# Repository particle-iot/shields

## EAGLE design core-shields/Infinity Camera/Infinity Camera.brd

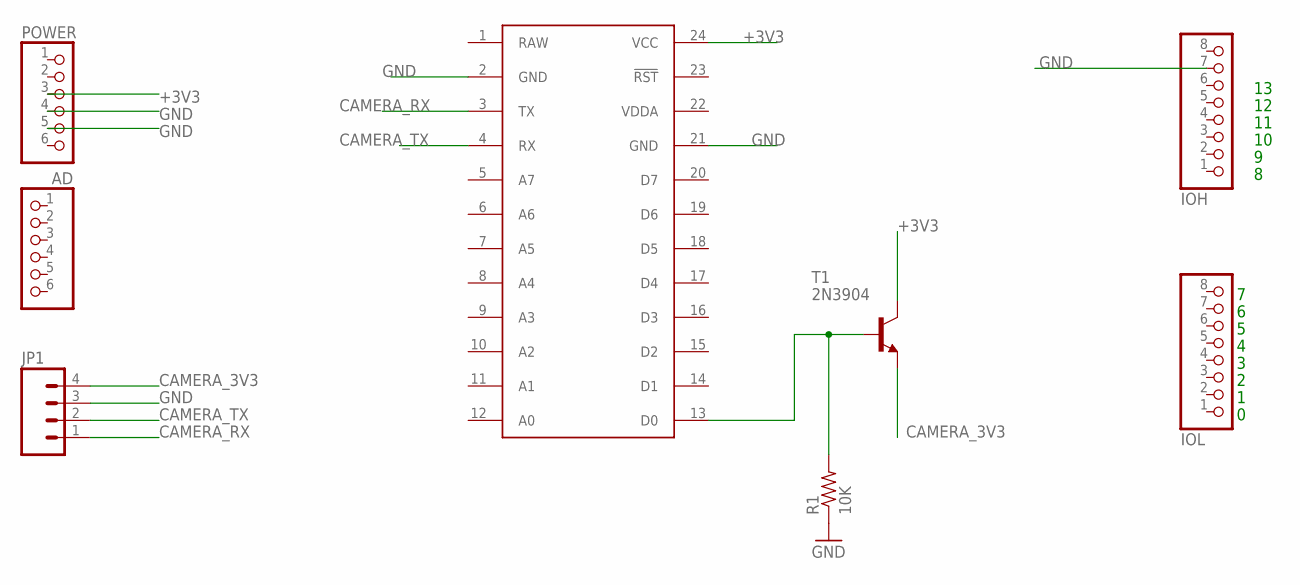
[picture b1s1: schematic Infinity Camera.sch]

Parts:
AD: PINHD-1X6; 1X06
IOH: PINHD-1X8; 1X08
IOL: PINHD-1X8; 1X08
JP1: M04PTH; 1X04
POWER: PINHD-1X6; 1X06
R1: 10K; AXIAL-0.4
T1: 2N3904; TO92
U$1: SPARK_CORECORE; SPARK_CORE

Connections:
+3V3: POWER.3, T1.1 (C), U$1.24 (VCC)
CAMERA_3V3: JP1.4, T1.3 (E)
CAMERA_RX: JP1.1, U$1.3 (TX)
CAMERA_TX: JP1.2, U$1.4 (RX)
GND: IOH.7, JP1.3, POWER.4, POWER.5, R1.P$1 (1), U$1.2 (GND), U$1.21 (GND)
unnamed: R1.P$2 (2), T1.2 (B), U$1.13 (D0)
RAW: U$1.1 (RAW)
VDDA: U$1.22 (VDDA)

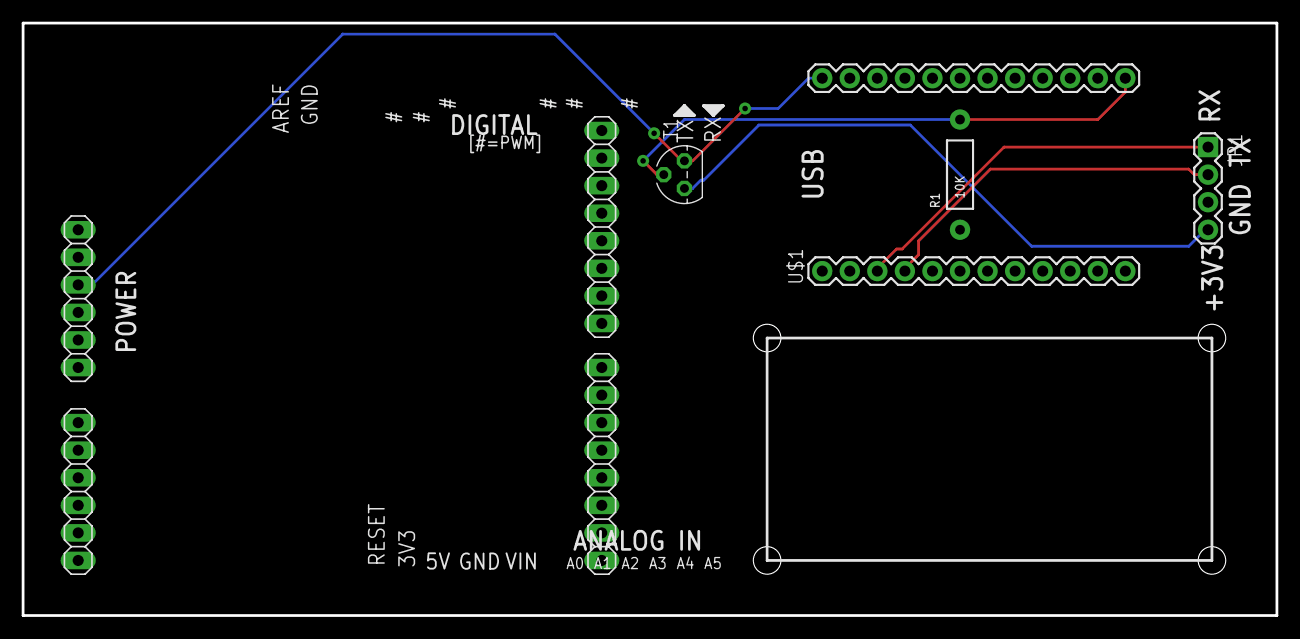
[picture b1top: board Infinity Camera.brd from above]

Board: 2 copper layers, 115.6 x 54.6 mm, 10 parts (0 on the bottom side), 6 nets.

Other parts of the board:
U$2, U$3: SPARK_LOGO

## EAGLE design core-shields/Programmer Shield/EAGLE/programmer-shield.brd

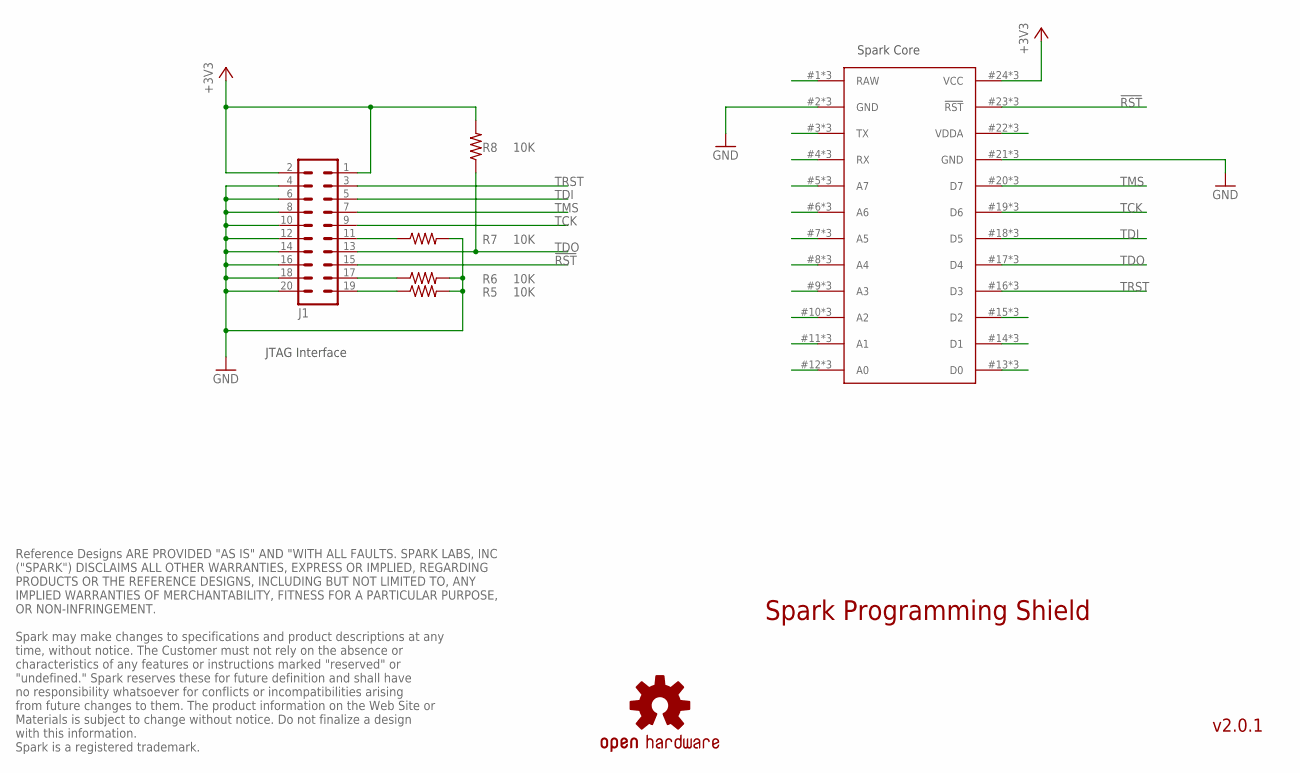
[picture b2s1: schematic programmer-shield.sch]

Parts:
J1: ML20
LOGO1: OSHW-LOGOM; OSHW-LOGO-M
R5, R6, R7, R8: 10K; AXIAL-0.3
U$1: SPARK_CORE; SPARK_CORE_STACKABLE

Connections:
!RST: J1.15, U$1.23 (!RST), U$1.#23 (!RST), U$1.@23 (!RST)
+3V3: J1.1, J1.2, R8.P$2 (2), U$1.24 (VCC), U$1.#24 (VCC), U$1.@24 (VCC)
GND: J1.4, J1.6, J1.8, J1.10, J1.12, J1.14, J1.16, J1.18, J1.20, R5.P$2 (2), R6.P$2 (2), R7.P$2 (2), U$1.2 (GND), U$1.21 (GND), U$1.#2 (GND), U$1.#21 (GND), U$1.@2 (GND), U$1.@21 (GND)
unnamed: U$1.1 (RAW), U$1.#1 (RAW), U$1.@1 (RAW)
unnamed: U$1.3 (TX), U$1.#3 (TX), U$1.@3 (TX)
unnamed: U$1.4 (RX), U$1.#4 (RX), U$1.@4 (RX)
unnamed: U$1.5 (A7), U$1.#5 (A7), U$1.@5 (A7)
unnamed: U$1.6 (A6), U$1.#6 (A6), U$1.@6 (A6)
unnamed: U$1.7 (A5), U$1.#7 (A5), U$1.@7 (A5)
unnamed: U$1.8 (A4), U$1.#8 (A4), U$1.@8 (A4)
unnamed: U$1.9 (A3), U$1.#9 (A3), U$1.@9 (A3)
unnamed: U$1.10 (A2), U$1.#10 (A2), U$1.@10 (A2)
unnamed: U$1.11 (A1), U$1.#11 (A1), U$1.@11 (A1)
unnamed: U$1.12 (A0), U$1.#12 (A0), U$1.@12 (A0)
unnamed: U$1.13 (D0), U$1.#13 (D0), U$1.@13 (D0)
unnamed: J1.19, R5.P$1 (1)
unnamed: J1.17, R6.P$1 (1)
unnamed: J1.11, R7.P$1 (1)
unnamed: U$1.14 (D1), U$1.#14 (D1), U$1.@14 (D1)
unnamed: U$1.15 (D2), U$1.#15 (D2), U$1.@15 (D2)
unnamed: U$1.22 (VDDA), U$1.#22 (VDDA), U$1.@22 (VDDA)
TCK: J1.9, U$1.19 (D6), U$1.#19 (D6), U$1.@19 (D6)
TDI: J1.5, U$1.18 (D5), U$1.#18 (D5), U$1.@18 (D5)
TDO: J1.13, R8.P$1 (1), U$1.17 (D4), U$1.#17 (D4), U$1.@17 (D4)
TMS: J1.7, U$1.20 (D7), U$1.#20 (D7), U$1.@20 (D7)
TRST: J1.3, U$1.16 (D3), U$1.#16 (D3), U$1.@16 (D3)

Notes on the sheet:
JTAG Interface
Spark Core
Spark Programming Shield
v2.0.1
Reference Designs ARE PROVIDED "AS IS" AND "WITH ALL FAULTS. SPARK LABS, INC ("SPARK") DISCLAIMS ALL OTHER WARRANTIES, EXPRESS OR IMPLIED, REGARDING PRODUCTS OR THE REFERENCE DESIGNS, INCLUDING BUT NOT LIMITED TO, ANY IMPLIED WARRANTIES OF MERCHANTABILITY, FITNESS FOR A PARTICULAR PURPOSE, OR NON-I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

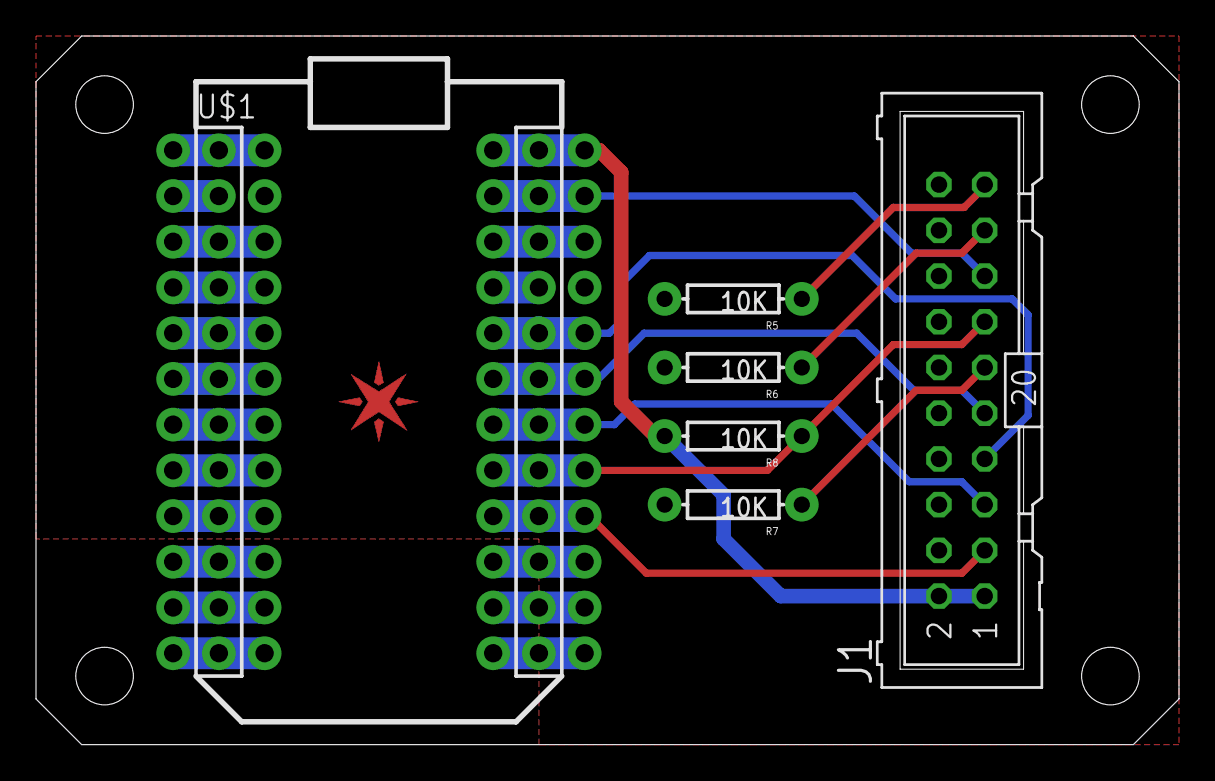
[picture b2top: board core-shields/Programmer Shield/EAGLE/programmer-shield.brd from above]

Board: 2 copper layers, 63.5 x 39.4 mm, 8 parts (1 on the bottom side), 26 nets.

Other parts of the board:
E$1: SPARK_LOGO_PLUS_PLANE

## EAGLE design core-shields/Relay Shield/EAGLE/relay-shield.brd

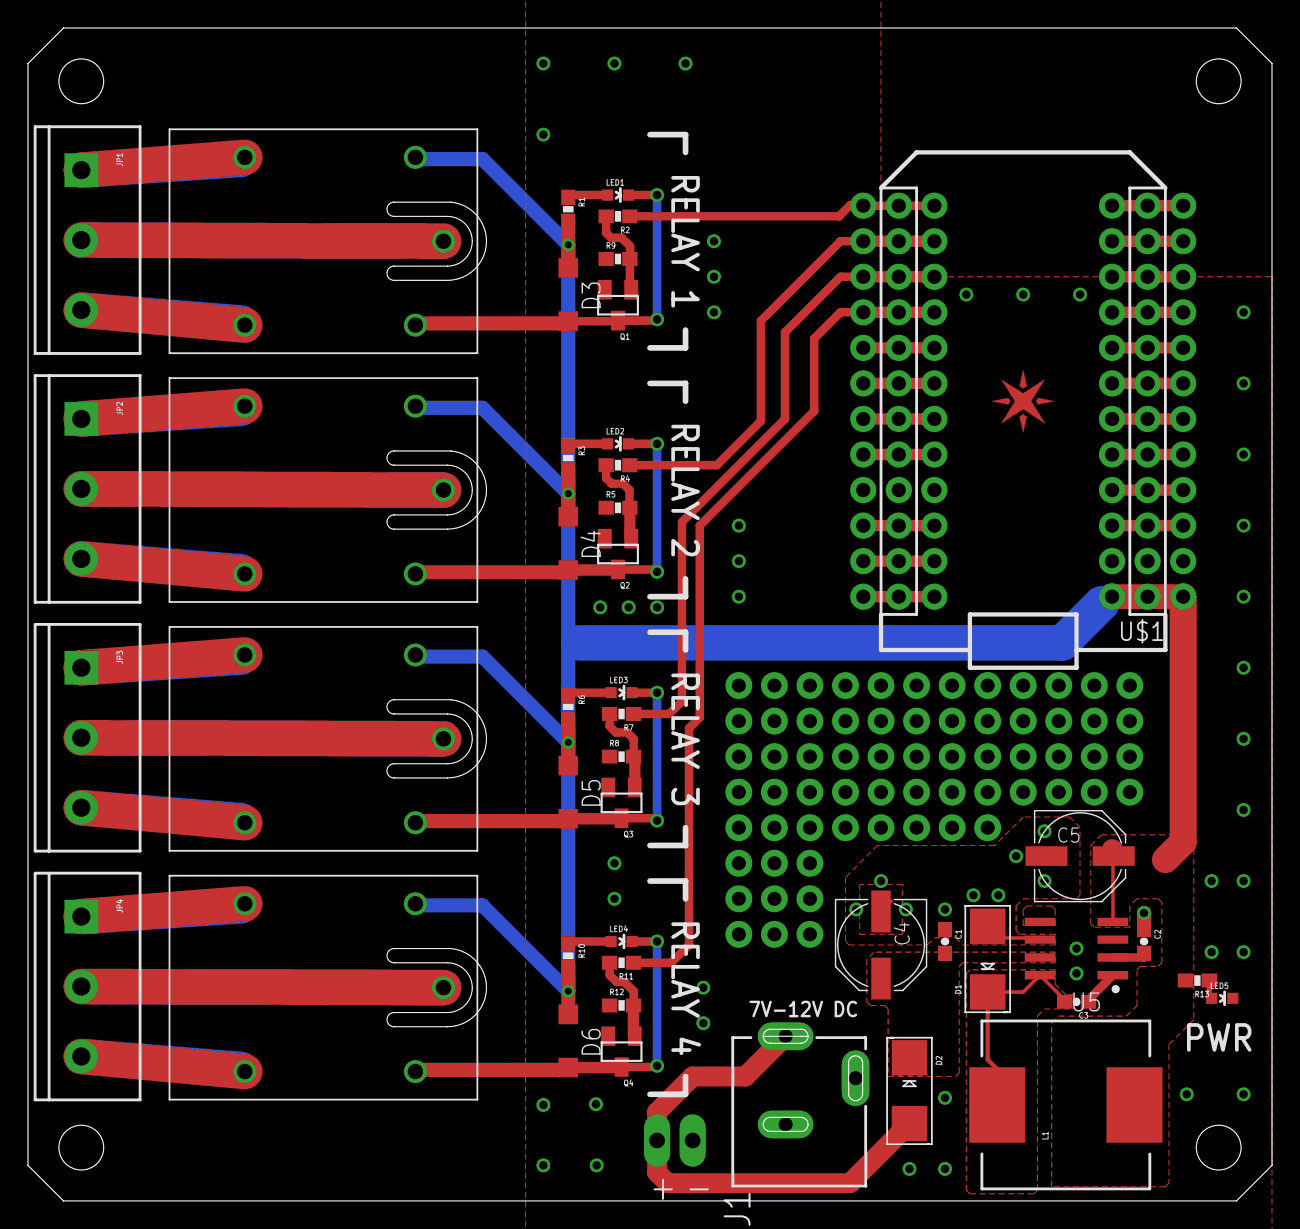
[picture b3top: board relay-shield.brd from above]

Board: 2 copper layers, 88.9 x 83.8 mm, 48 parts (1 on the bottom side), 53 nets.

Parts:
C1: 0.1uF; 0603-CAP
C2, C3: 10nF; 0603-CAP
C4: 100uF, 16V; PANASONIC_D
C5: 56uF, 10V; PANASONIC_D
D1, D2: B230; SMADIODE
D3, D4, D5, D6: SOD123
E$1: SPARK_LOGO_PLUS_PLANE
J1: POWER_JACKSLT; POWER_JACK_SLOT
JP1, JP2, JP3, JP4: SCREWTERMINAL-5MM-3
JP5: M02PTH3; 1X02_LONGPADS
L1: CDRH125NP-470M; CDRH125
LED1, LED2, LED3, LED4: RED; LED-0603
LED5: BLUE; LED-0603
LOGO1: OSHW-LOGOM; OSHW-LOGO-M
Q1, Q2, Q3, Q4: MPSA42; SOT23
R1, R2, R3, R4, R6, R7, R10, R11, R13: 1K; 0603-RES
R5, R8, R9, R12: 10K; 0603-RES
U1, U2, U3, U4: RELAYPANASONIC-JS; JS1-5V-F
U5: LM2672; SO08
U$1: SPARK_CORE; SPARK_CORE_STACKABLE

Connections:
+5V: C5.+, D3.C, D4.C, D5.C, D6.C, L1.2, R1.2, R3.2, R6.2, R10.2, R13.2, U1.COIL1, U2.COIL1, U3.COIL1, U4.COIL1, U5.4, U$1.1, U$1.#1, U$1.@1
GND: C1.1, C2.1, C4.-, C5.-, D1.A, J1.GND@1, J1.GND@2, JP5.1, LED5.C, Q1.2, Q2.2, Q3.2, Q4.2, R5.1, R8.1, R9.1, R12.1, U5.6, U$1.2, U$1.21, U$1.#2, U$1.#21, U$1.@2, U$1.@21
MAIN1: JP1.2, U1.COMMON
MAIN2: JP2.2, U2.COMMON
MAIN3: JP3.2, U3.COMMON
MAIN4: JP4.2, U4.COMMON
unnamed: D3.A, LED1.C, Q1.3, U1.COIL2
unnamed: Q2.1, R4.2, R5.2
unnamed: Q1.1, R2.2, R9.2
unnamed: LED1.A, R1.1
unnamed: D4.A, LED2.C, Q2.3, U2.COIL2
unnamed: LED2.A, R3.1
unnamed: Q3.1, R7.2, R8.2
unnamed: D5.A, LED3.C, Q3.3, U3.COIL2
unnamed: LED3.A, R6.1
unnamed: Q4.1, R11.2, R12.2
unnamed: D6.A, LED4.C, Q4.3, U4.COIL2
unnamed: LED4.A, R10.1
unnamed: U$1.17, U$1.#17, U$1.@17
unnamed: C1.2, C4.+, D2.C, U5.7
unnamed: U$1.18, U$1.#18, U$1.@18
unnamed: LED5.A, R13.1
unnamed: U$1.19, U$1.#19, U$1.@19
unnamed: U$1.20, U$1.#20, U$1.@20
unnamed: U$1.22, U$1.#22, U$1.@22
unnamed: U$1.23, U$1.#23, U$1.@23
unnamed: U$1.24, U$1.#24, U$1.@24
unnamed: U$1.12, U$1.#12, U$1.@12
unnamed: U$1.11, U$1.#11, U$1.@11
unnamed: U$1.10, U$1.#10, U$1.@10
unnamed: U$1.9, U$1.#9, U$1.@9
unnamed: U$1.8, U$1.#8, U$1.@8
unnamed: U$1.7, U$1.#7, U$1.@7
unnamed: U$1.6, U$1.#6, U$1.@6
unnamed: U$1.5, U$1.#5, U$1.@5
unnamed: U$1.4, U$1.#4, U$1.@4
unnamed: U$1.3, U$1.#3, U$1.@3
unnamed: D2.A, J1.PWR, JP5.2
unnamed: C3.1, U5.1
unnamed: C3.2, D1.C, L1.1, U5.8
unnamed: C2.2, U5.2
NC1: JP1.3, U1.CLOSED
NC2: JP2.3, U2.CLOSED
NC3: JP3.3, U3.CLOSED
NC4: JP4.3, U4.CLOSED
NO1: JP1.1, U1.OPEN
NO2: JP2.1, U2.OPEN
NO3: JP3.1, U3.OPEN
NO4: JP4.1, U4.OPEN
RELAY1: R2.1, U$1.13, U$1.#13, U$1.@13
RELAY2: R4.1, U$1.14, U$1.#14, U$1.@14
RELAY3: R7.1, U$1.15, U$1.#15, U$1.@15
RELAY4: R11.1, U$1.16, U$1.#16, U$1.@16

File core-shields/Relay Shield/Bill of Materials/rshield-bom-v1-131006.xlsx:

| PROJECT NAME |  | SPARK RELAY SHIELD
 | LAST UPDATED |  | 41554
 | RSHIELD
 | Qty | AQS P/N | Device | Minimum Specification | Component Value (if different) | Package/Case | Designator | AVL | AVL P/N | Additional Comments
 | 1 | 307-20-301623 | Fab PCB | Single Sided, 1.6mm, 1OZ, Electroless Nickel Immersion Gold, White Solder Mask,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 |  |  |  |  |  | CONSIGNED BY SPARK
 | 1 | HL-121-08-301869 | Capacitor | 10nF, 10%, 10V |  | 0603 | C4 | AVX | 0603ZC103KAT2A
 | 2 | HL-201-40-101081 | Diode | 30V, 2A |  | DO-214 | D1, D2 | Diodes, Inc. | B230A-13-F
 | 4 | HL-201-50-301081 | Diode | 0.15A |  | SOD123 | D5-D8 | Arrow | 1N4148
 | 2 | HL-515-30-301994 | Female Header | Single String, 0.230" Mating Length |  | 0.1", 12 pin | JP5, JP6 | Kaweei | CS25401-12G-S85-C 
 | 1 | HL-161-53-301137 | Inductor | 47uH Power Inductor, SMD |  | 12.7mm x 10mm | L1 | Bourns, Inc. | SDR1005-470KL
 | 1 |  | LED | Blue |  | 0603 | LED5 | Wenliang | WLUB0603A-341
 | 4 | HL-414-10-301296 | LED | Red |  | 0603 | LED1-LED4 | Wenliang | WLUE0603A-25
 | 4 | HL-211-60-301212 | NPN Transistor | 300V |  | SOT23 | Q1-Q4 | Micro Commercial | MMBTA42-TP
 | 1 | HL-121-36-301178 | Polarized Capacitor | 100uF, 10V, 20% |  | 6.3mm diameter, SMT | C6 | Panasonic Electronic Components | EEE-1AA101SP
 | 1 | HL-121-64-301147 | Polarized Capacitor | 47uF, 25V, 20% |  | 6.3mm diameter, SMT | C5 | Panasonic Electronic Components | EEE-1EA470WP
 | 1 | HL-515-50-301064 | Power Barrel Jack Connector |  |  | Through-hole, 3 contacts | J1 | Kaweei | TDC-005-20
 | 4 | HL-105-10-301382 | Resistor | 10K, 1/4W, 5% |  | 0603 | R5, R8, R9, R12 | Rohm Semiconductor | ESR03EZPJ103
 | 9 | HL-101-15-303050 | Resistor | 1K, 1/4W, 5% |  | 0603 | R1-R4, R6-R7, R10-R11, R13 | Rohm Semiconductor | ESR03EZPJ102
 | 4 | HL-511-30-301384 | Screw Terminal | M03, 10A, green |  | 5mm pitch, 3 pin | JP1, JP2, JP3, JP4 | Boda | PA001-5.0-3P
 | 4 | 418-20-301016 | SPDT Relay | 10A, 250VAC/25VDC |  | COM-00101 | U1-U4 | Verical | JS1-5V-F | CONSIGNED BY SPARK
 | 1 | HL-221-28-301648 | Voltage Regulator | Buck Regulator, 5V, 2A |  | 8-SOP | U6 | Diodes, Inc. | AP1509-50SG-13
 | PACKAGING
 | Qty |  | Device | Minimum Specification | Component Value (if different) | Package/Case | Designator | AVL | AVL P/N | Additional Comments
 | 1 | HL-901-00-301328 | Large Static Bag |  |  | 160 x 130mm
 | 1 | HL-901-00-301333 | Large Static Bubble Bag |  |  | 170 x 140mm, red
 | 1 | 831-10-301390 | "STICK-RS" sticker | Shield Description and UPC Barcode |  | 8 x 10 cm |  |  |  | CONSIGNED BY SPARK

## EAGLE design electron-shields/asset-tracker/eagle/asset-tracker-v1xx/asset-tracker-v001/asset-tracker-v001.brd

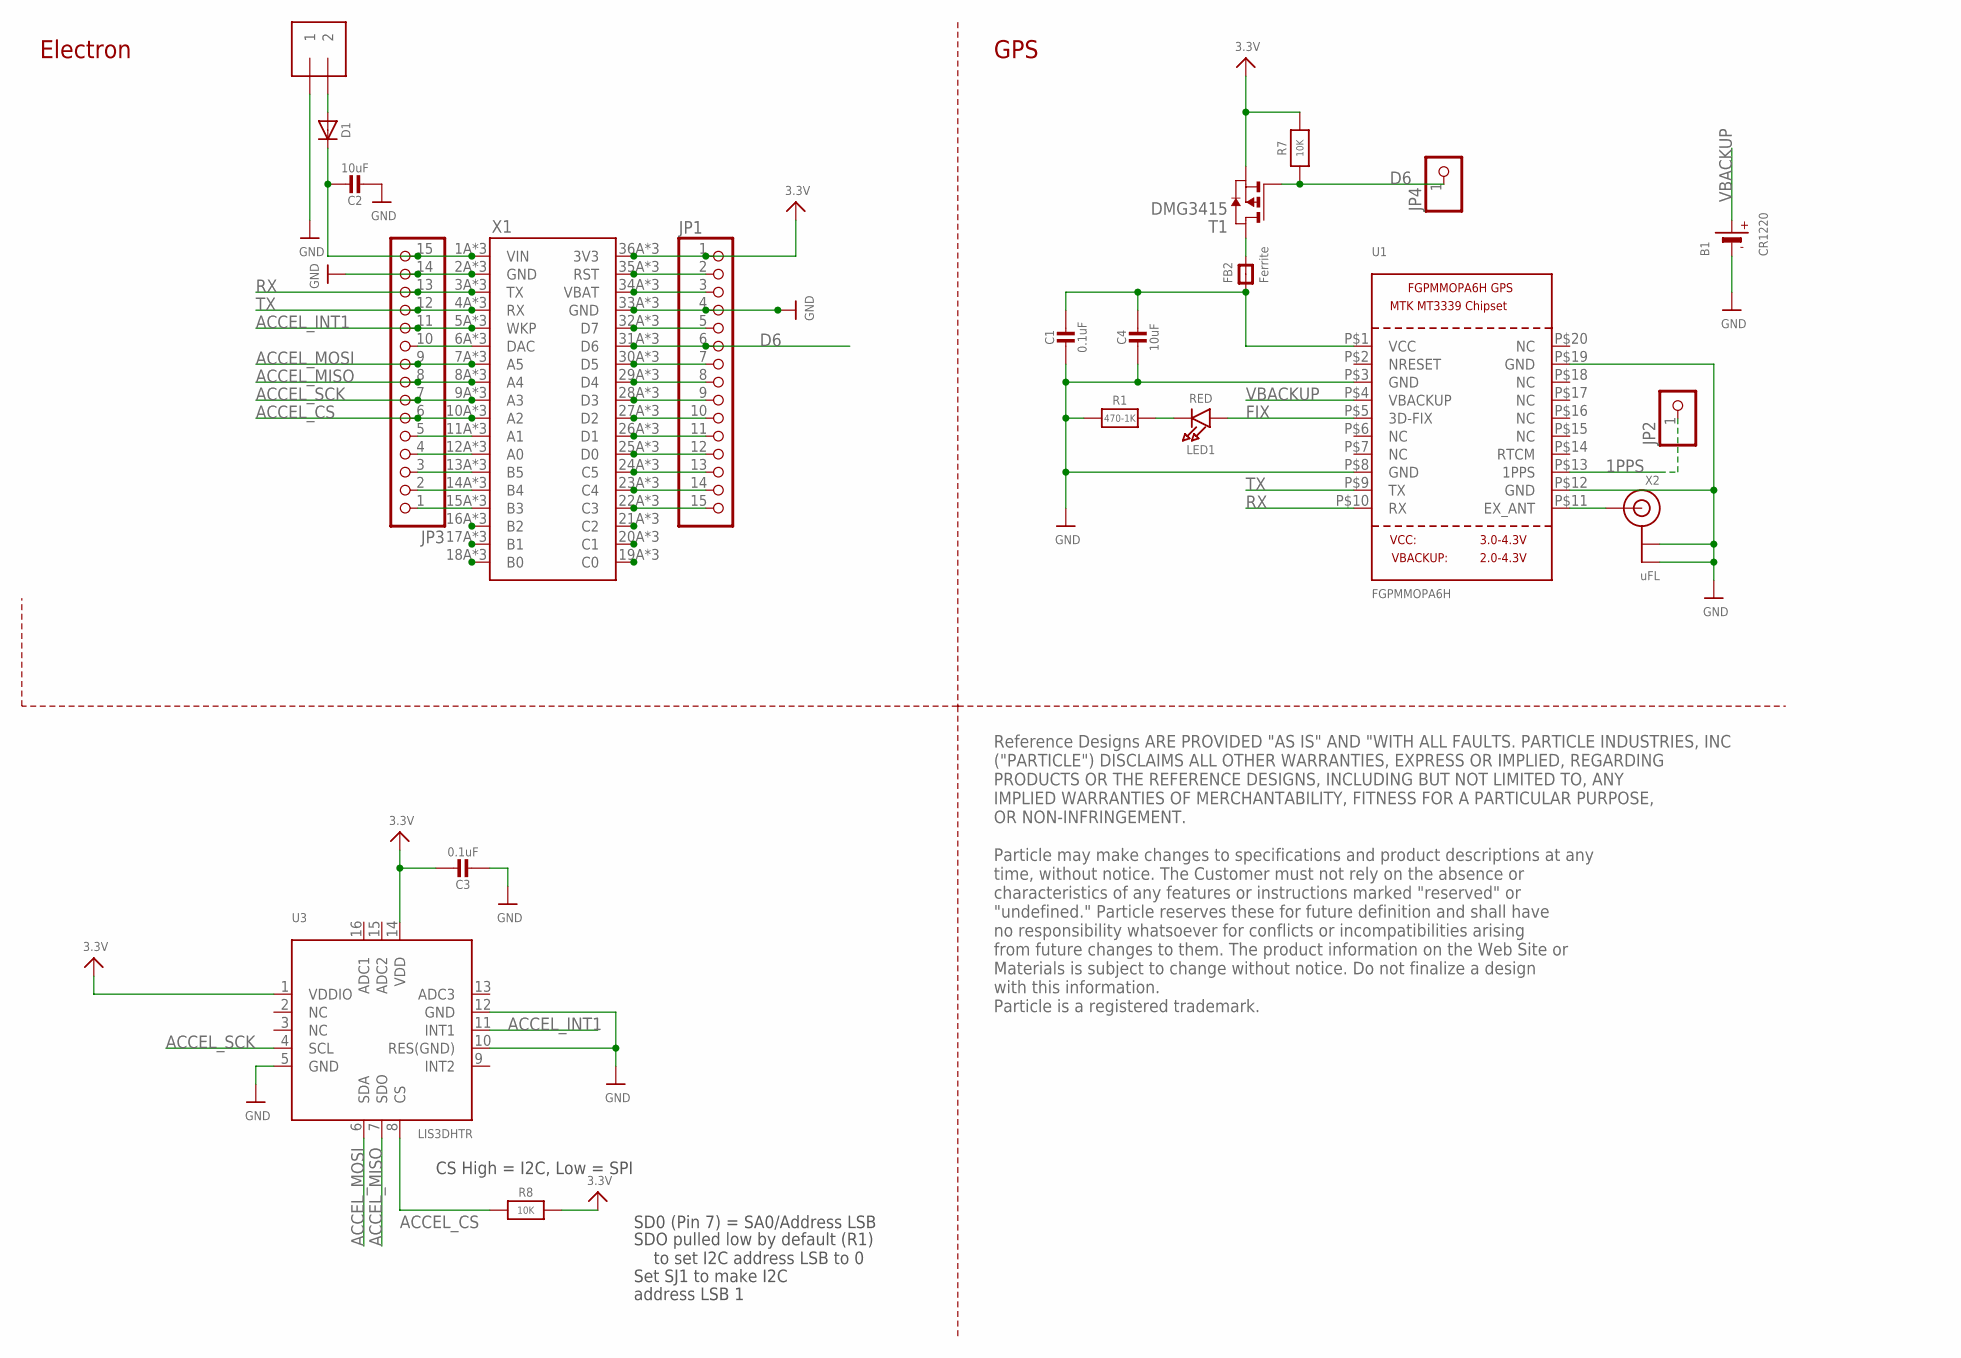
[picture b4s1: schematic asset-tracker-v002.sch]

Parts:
B1: CR1220
C1: 0.1uF; 0805-NO@1
C2, C4: 10uF; 0805-NO@1
C3: 0.1uF; 0805_10MGAP
D1: DIODESMA; SMADIODE
FB2: Ferrite; 0805-NO@1
J1: 1X2-3.5MM
JP1, JP3: HEADER-1X15; 1X15_ROUND_70
JP2, JP4: HEADER-1X1ROUND; 1X01_ROUND
LED1: RED; CHIPLED_0805_NOOUTLINE
R1: 470-1K; 0805-NO
R7, R8: 10K; 0805-NO
T1: DMG3415; SOT-23
U1: FGPMMOPA6H
U3: LIS3DHTR; LGA16_3X3MM
X1: ELECTRON; ELECTRON_SMT
X2: uFL; U.FL

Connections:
1PPS: JP2.1, U1.P$13 (1PPS)
3.3V: C3.1, JP1.1, R7.2, R8.2, T1.2 (S), U3.1 (VDDIO), U3.14 (VDD), X1.36A (3V3), X1.36B (3V3), X1.36C (3V3)
A0: JP3.4, X1.12A (A0), X1.12B (A0), X1.12C (A0)
A1: JP3.5, X1.11A (A1), X1.11B (A1), X1.11C (A1)
ACCEL_CS: JP3.6, R8.1, U3.8 (CS), X1.10A (A2), X1.10B (A2), X1.10C (A2)
ACCEL_INT1: JP3.11, U3.11 (INT1), X1.5A (WKP), X1.5B (WKP), X1.5C (WKP)
ACCEL_MISO: JP3.8, U3.7 (SDO), X1.8A (A4), X1.8B (A4), X1.8C (A4)
ACCEL_MOSI: JP3.9, U3.6 (SDA), X1.7A (A5), X1.7B (A5), X1.7C (A5)
ACCEL_SCK: JP3.7, U3.4 (SCL), X1.9A (A3), X1.9B (A3), X1.9C (A3)
B3: JP3.1, X1.15A (B3), X1.15B (B3), X1.15C (B3)
B4: JP3.2, X1.14A (B4), X1.14B (B4), X1.14C (B4)
B5: JP3.3, X1.13A (B5), X1.13B (B5), X1.13C (B5)
C3: JP1.15, X1.22A (C3), X1.22B (C3), X1.22C (C3)
C4: JP1.14, X1.23A (C4), X1.23B (C4), X1.23C (C4)
C5: JP1.13, X1.24A (C5), X1.24B (C5), X1.24C (C5)
D0: JP1.12, X1.25A (D0), X1.25B (D0), X1.25C (D0)
D1: JP1.11, X1.26A (D1), X1.26B (D1), X1.26C (D1)
D2: JP1.10, X1.27A (D2), X1.27B (D2), X1.27C (D2)
D3: JP1.9, X1.28A (D3), X1.28B (D3), X1.28C (D3)
D4: JP1.8, X1.29A (D4), X1.29B (D4), X1.29C (D4)
D5: JP1.7, X1.30A (D5), X1.30B (D5), X1.30C (D5)
D6: JP1.6, JP4.1, R7.1, T1.3 (G), X1.31A (D6), X1.31B (D6), X1.31C (D6)
D7: JP1.5, X1.32A (D7), X1.32B (D7), X1.32C (D7)
DAC: JP3.10, X1.6A (DAC), X1.6B (DAC), X1.6C (DAC)
FIX: LED1.A, U1.P$5 (3D-FIX)
unnamed: C1.1, C4.1, FB2.1, U1.P$1 (VCC)
unnamed: LED1.C, R1.2
unnamed 28: U1.P$11 (EX_ANT), X2.3 (SIGNAL); also elsewhere on the board
unnamed: C2.1, D1.C, JP3.15, X1.1A (VIN), X1.1B (VIN), X1.1C (VIN)
unnamed: X1.16A (B2), X1.16B (B2), X1.16C (B2)
unnamed: X1.17A (B1), X1.17B (B1), X1.17C (B1)
unnamed: X1.18A (B0), X1.18B (B0), X1.18C (B0)
unnamed: X1.21A (C2), X1.21B (C2), X1.21C (C2)
unnamed: X1.20A (C1), X1.20B (C1), X1.20C (C1)
unnamed: X1.19A (C0), X1.19B (C0), X1.19C (C0)
RST: JP1.2, X1.35A (RST), X1.35B (RST), X1.35C (RST)
RX: JP3.13, U1.P$10 (RX), X1.3A (TX), X1.3B (TX), X1.3C (TX)
TX: JP3.12, U1.P$9 (TX), X1.4A (RX), X1.4B (RX), X1.4C (RX)
VBACKUP: B1.+$1 (+), U1.P$4 (VBACKUP); also elsewhere on the board
VBAT: JP1.3, X1.34A (VBAT), X1.34B (VBAT), X1.34C (VBAT)
VCC: FB2.2, T1.1 (D)

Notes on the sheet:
SD0 (Pin 7) = SA0/Address LSB
CS High = I2C, Low = SPI
SDO pulled low by default (R1) to set I2C address LSB to 0
Set SJ1 to make I2C
address LSB 1
GPS
Electron
Reference Designs ARE PROVIDED "AS IS" AND "WITH ALL FAULTS. PARTICLE INDUSTRIES, INC ("PARTICLE") DISCLAIMS ALL OTHER WARRANTIES, EXPRESS OR IMPLIED, REGARDING PRODUCTS OR THE REFERENCE DESIGNS, INCLUDING BUT NOT LIMITED TO, ANY IMPLIED WARRANTIES OF MERCHANTABILITY, FITNESS FOR A PARTICULAR PURPO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

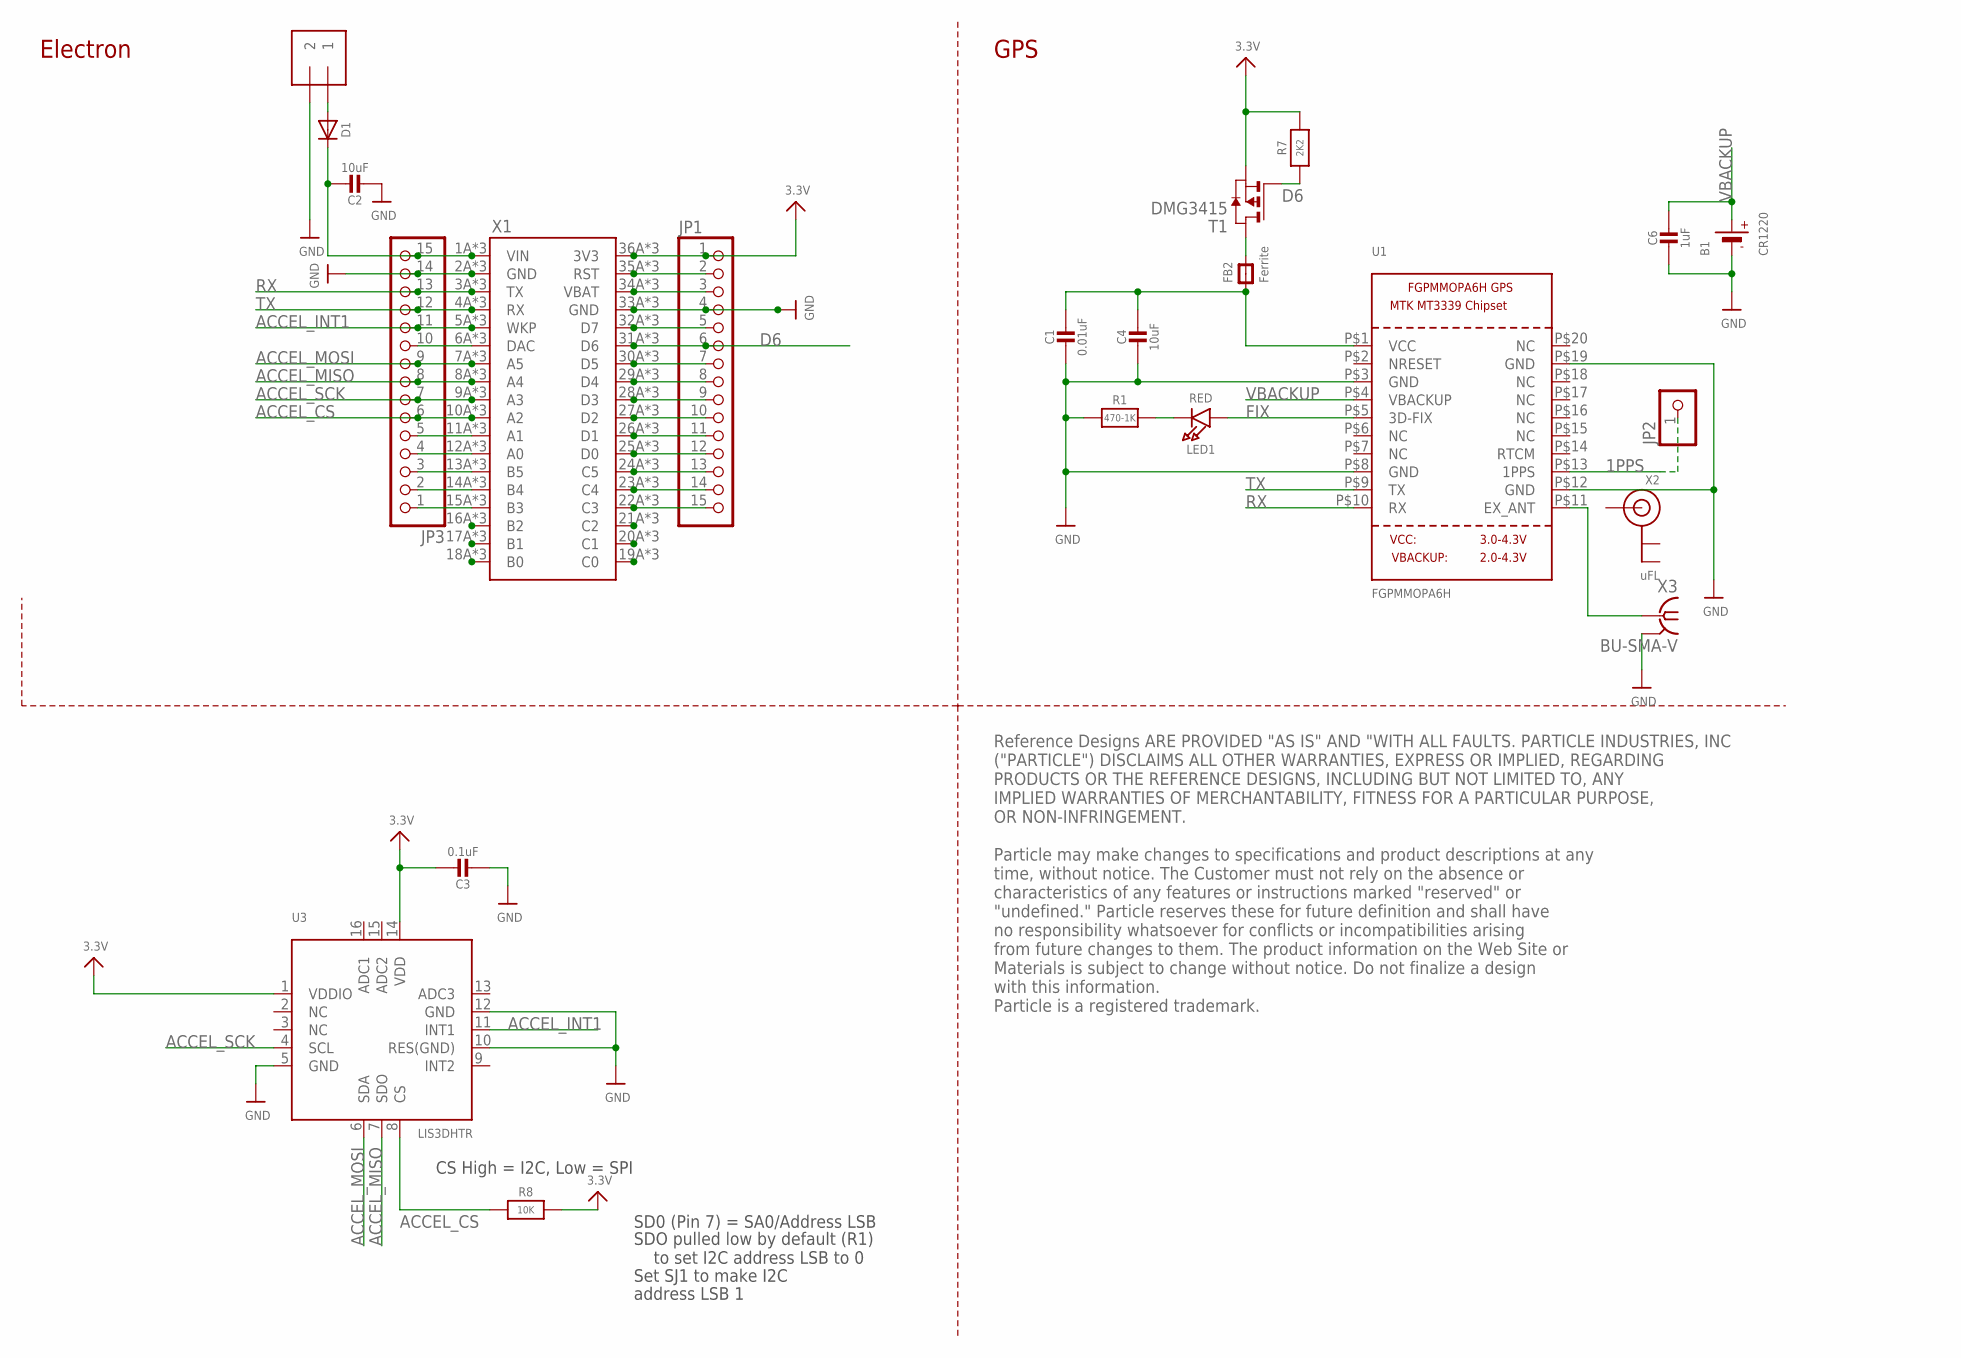
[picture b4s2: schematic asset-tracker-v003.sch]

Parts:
B1: CR1220
C1: 0.01uF; 0805-NO@1
C2, C4: 10uF; 0805-NO@1
C3: 0.1uF; 0805_10MGAP
C6: 1uF; 0805-NO@1
D1: DIODESMA; SMADIODE
FB2: Ferrite; 0805-NO@1
J1: 1X2-3.5MM
JP1, JP3: HEADER-1X15; 1X15_ROUND_70
JP2: HEADER-1X1ROUND; 1X01_ROUND
LED1: RED; CHIPLED_0805_NOOUTLINE
R1: 470-1K; 0805-NO
R7: 2K2; 0805-NO
R8: 10K; 0805-NO
T1: DMG3415; SOT-23
U1: FGPMMOPA6H
U3: LIS3DHTR; LGA16_3X3MM
X1: ELECTRON; ELECTRON_SMT
X2: uFL; U.FL
X3: BU-SMA-V

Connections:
1PPS: JP2.1, U1.P$13 (1PPS)
3.3V: C3.1, JP1.1, R7.2, R8.2, T1.2 (S), U3.1 (VDDIO), U3.14 (VDD), X1.36A (3V3), X1.36B (3V3), X1.36C (3V3)
A0: JP3.4, X1.12A (A0), X1.12B (A0), X1.12C (A0)
A1: JP3.5, X1.11A (A1), X1.11B (A1), X1.11C (A1)
ACCEL_CS: JP3.6, R8.1, U3.8 (CS), X1.10A (A2), X1.10B (A2), X1.10C (A2)
ACCEL_INT1: JP3.11, U3.11 (INT1), X1.5A (WKP), X1.5B (WKP), X1.5C (WKP)
ACCEL_MISO: JP3.8, U3.7 (SDO), X1.8A (A4), X1.8B (A4), X1.8C (A4)
ACCEL_MOSI: JP3.9, U3.6 (SDA), X1.7A (A5), X1.7B (A5), X1.7C (A5)
ACCEL_SCK: JP3.7, U3.4 (SCL), X1.9A (A3), X1.9B (A3), X1.9C (A3)
B3: JP3.1, X1.15A (B3), X1.15B (B3), X1.15C (B3)
B4: JP3.2, X1.14A (B4), X1.14B (B4), X1.14C (B4)
B5: JP3.3, X1.13A (B5), X1.13B (B5), X1.13C (B5)
C3: JP1.15, X1.22A (C3), X1.22B (C3), X1.22C (C3)
C4: JP1.14, X1.23A (C4), X1.23B (C4), X1.23C (C4)
C5: JP1.13, X1.24A (C5), X1.24B (C5), X1.24C (C5)
D0: JP1.12, X1.25A (D0), X1.25B (D0), X1.25C (D0)
D1: JP1.11, X1.26A (D1), X1.26B (D1), X1.26C (D1)
D2: JP1.10, X1.27A (D2), X1.27B (D2), X1.27C (D2)
D3: JP1.9, X1.28A (D3), X1.28B (D3), X1.28C (D3)
D4: JP1.8, X1.29A (D4), X1.29B (D4), X1.29C (D4)
D5: JP1.7, X1.30A (D5), X1.30B (D5), X1.30C (D5)
D6: JP1.6, R7.1, T1.3 (G), X1.31A (D6), X1.31B (D6), X1.31C (D6); also elsewhere on the board
D7: JP1.5, X1.32A (D7), X1.32B (D7), X1.32C (D7)
DAC: JP3.10, X1.6A (DAC), X1.6B (DAC), X1.6C (DAC)
FIX: LED1.A, U1.P$5 (3D-FIX)
unnamed: C1.1, C4.1, FB2.1, U1.P$1 (VCC)
unnamed: LED1.C, R1.2
unnamed 28: U1.P$11 (EX_ANT), X3.1; also elsewhere on the board
unnamed: C2.1, D1.C, JP3.15, X1.1A (VIN), X1.1B (VIN), X1.1C (VIN)
unnamed: X1.16A (B2), X1.16B (B2), X1.16C (B2)
unnamed: X1.17A (B1), X1.17B (B1), X1.17C (B1)
unnamed: X1.18A (B0), X1.18B (B0), X1.18C (B0)
unnamed: X1.21A (C2), X1.21B (C2), X1.21C (C2)
unnamed: X1.20A (C1), X1.20B (C1), X1.20C (C1)
unnamed: X1.19A (C0), X1.19B (C0), X1.19C (C0)
RST: JP1.2, X1.35A (RST), X1.35B (RST), X1.35C (RST)
RX: JP3.13, U1.P$10 (RX), X1.3A (TX), X1.3B (TX), X1.3C (TX)
TX: JP3.12, U1.P$9 (TX), X1.4A (RX), X1.4B (RX), X1.4C (RX)
VBACKUP: B1.+$1 (+), C6.1, U1.P$4 (VBACKUP)
VBAT: JP1.3, X1.34A (VBAT), X1.34B (VBAT), X1.34C (VBAT)
VCC: FB2.2, T1.1 (D)

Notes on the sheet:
SD0 (Pin 7) = SA0/Address LSB
CS High = I2C, Low = SPI
SDO pulled low by default (R1) to set I2C address LSB to 0
Set SJ1 to make I2C
address LSB 1
GPS
Electron
Reference Designs ARE PROVIDED "AS IS" AND "WITH ALL FAULTS. PARTICLE INDUSTRIES, INC ("PARTICLE") DISCLAIMS ALL OTHER WARRANTIES, EXPRESS OR IMPLIED, REGARDING PRODUCTS OR THE REFERENCE DESIGNS, INCLUDING BUT NOT LIMITED TO, ANY IMPLIED WARRANTIES OF MERCHANTABILITY, FITNESS FOR A PARTICULAR PURPO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

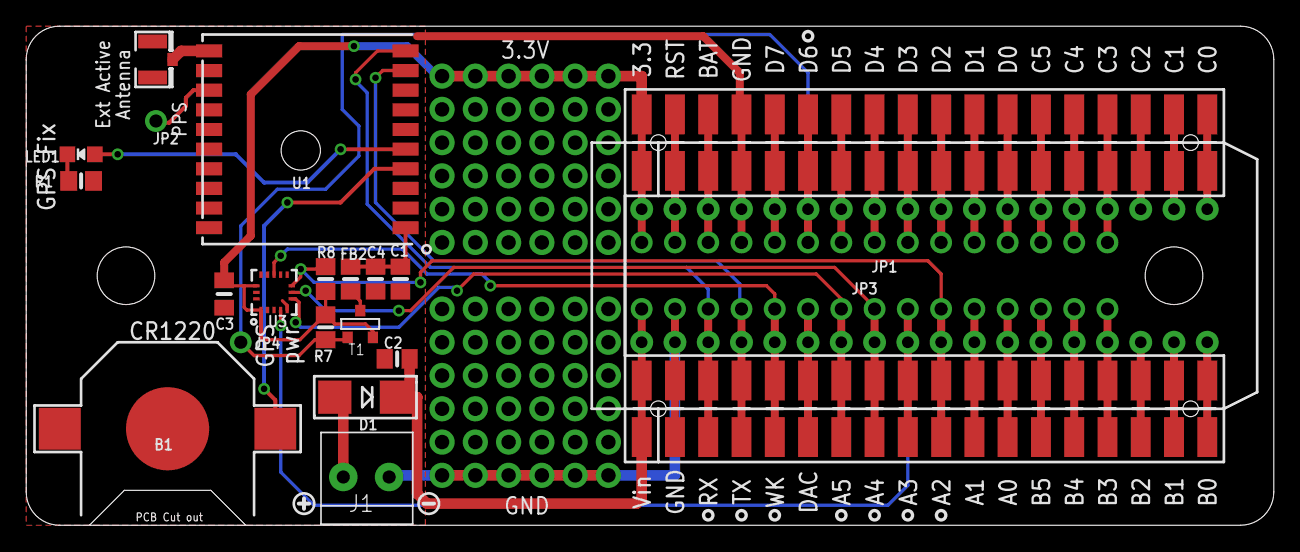
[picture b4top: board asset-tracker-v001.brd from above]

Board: 2 copper layers, 95.2 x 38.1 mm, 23 parts (0 on the bottom side), 43 nets.

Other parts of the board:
U$13: SYMBOL_MINUS
U$21: SYMBOL_PLUS

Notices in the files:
parts and their libraries:
SparkFun-Connectors: Licensing: CC v3.0 Share-Alike You are welcome to use this library for commercial purposes.
SparkFun-LED: Licensing: Creative Commons ShareAlike 4.0 International - https://creativecommons.org/licenses/by-sa/4.0
